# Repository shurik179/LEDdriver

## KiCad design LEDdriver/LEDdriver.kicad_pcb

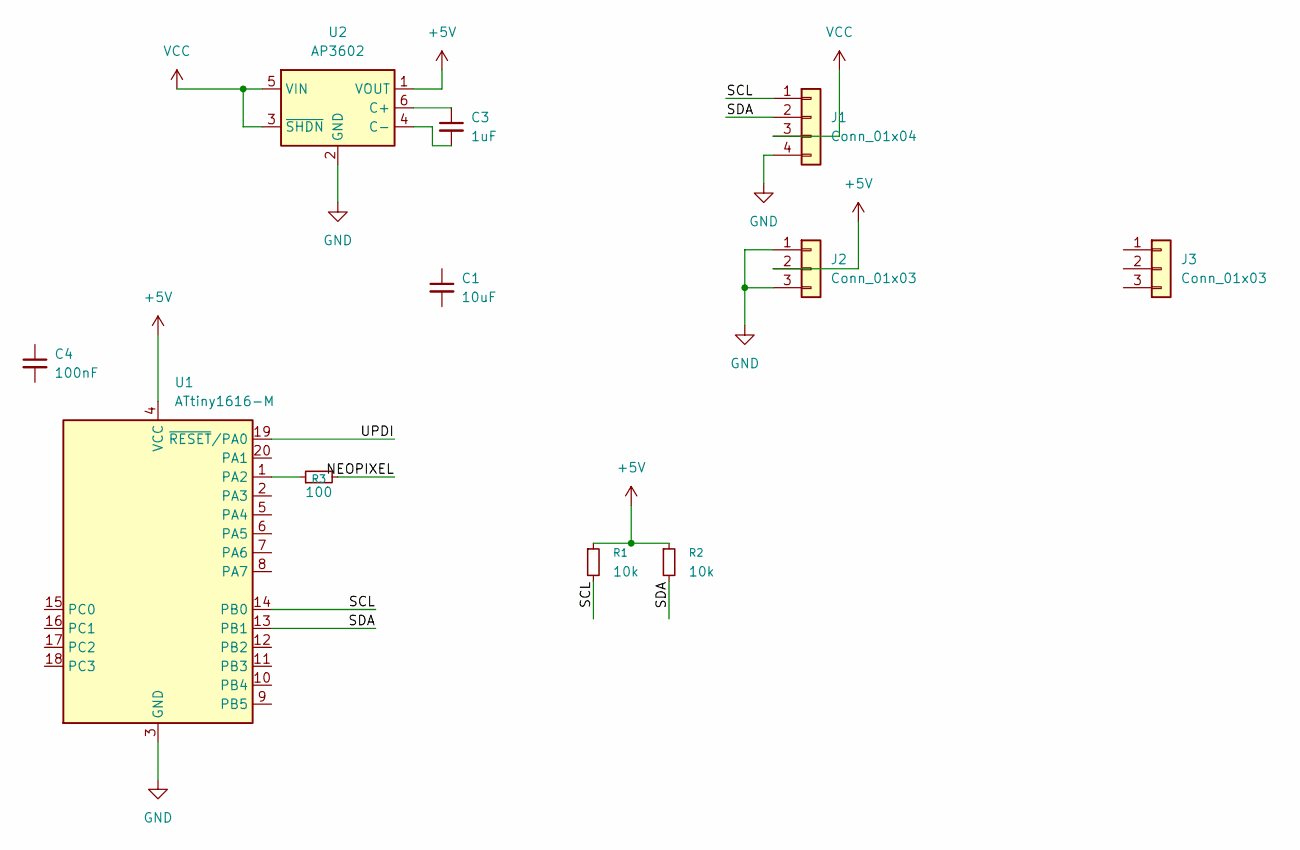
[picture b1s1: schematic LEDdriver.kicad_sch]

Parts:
C1: 10uF; C_0805_2012Metric
C3: 1uF; C_0603_1608Metric
C4: 100nF; C_0603_1608Metric
J1: Conn_01x04; JST_PH_S4B-PH-SM4-TB_1x04-1MP_P2.00mm_Horizontal
J2: Conn_01x03; PinHeader_1x03_P2.54mm_Horizontal
J3: Conn_01x03
R1, R2: 10k; R_0603_1608Metric
R3: 100; R_0603_1608Metric
U1: ATtiny1616-M; VQFN-20-1EP_3x3mm_P0.4mm_EP1.7x1.7mm
U2: AP3602; TSOT-23-6

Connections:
+5V: J2.2, R1.1, R2.1, U1.4 (VCC), U2.1 (VOUT)
/NEOPIXEL: R3.2
/SCL: J1.1, R1.2, U1.14 (PB0)
/SDA: J1.2, R2.2, U1.13 (PB1)
/UPDI: U1.19 (~RESET/PA0)
GND: J1.4, J2.1, J2.3, U1.3 (GND), U1.21 (GND), U2.2 (GND)
unnamed: R3.1, U1.1 (PA2)
unnamed: C3.1, U2.6 (C+)
unnamed: C3.2, U2.4 (C-)
VCC: J1.3, U2.3 (~SHDN), U2.5 (VIN)

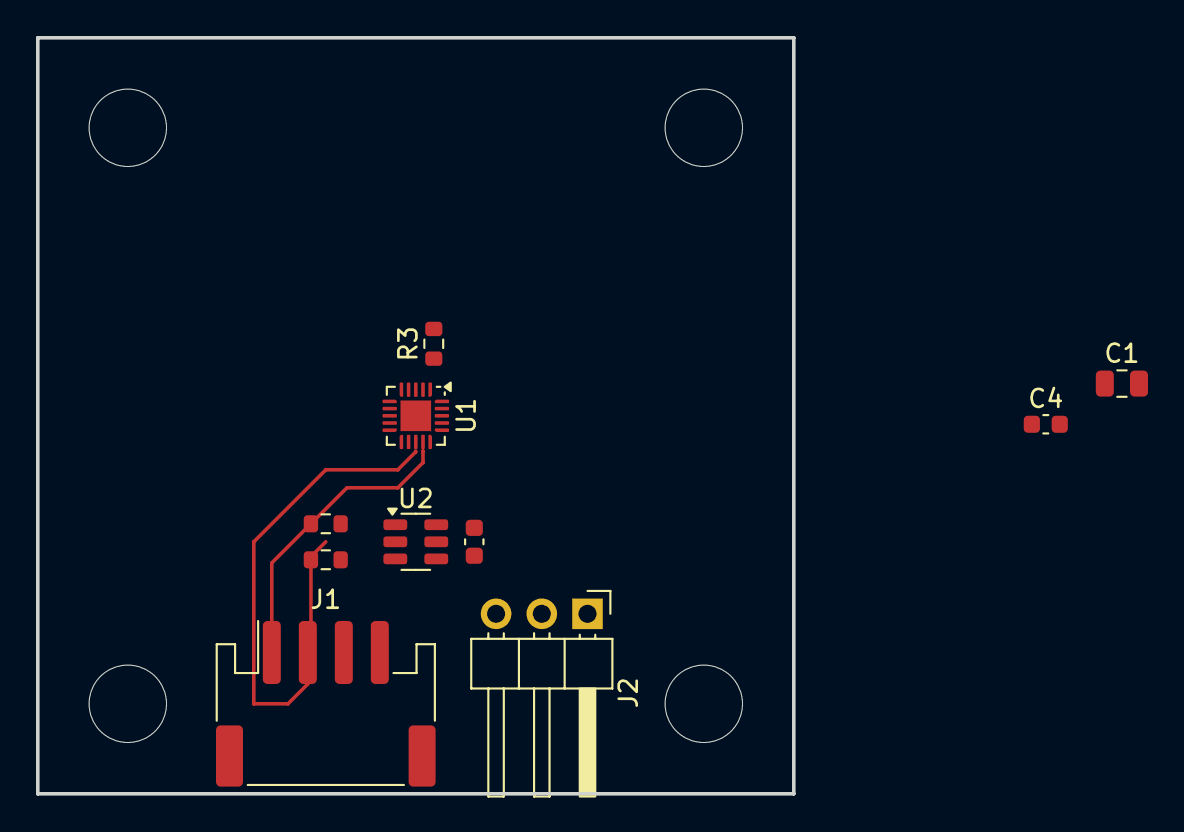
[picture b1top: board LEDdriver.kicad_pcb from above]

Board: 2 copper layers, 42.0 x 42.0 mm, 10 parts (0 on the bottom side), 8 nets.

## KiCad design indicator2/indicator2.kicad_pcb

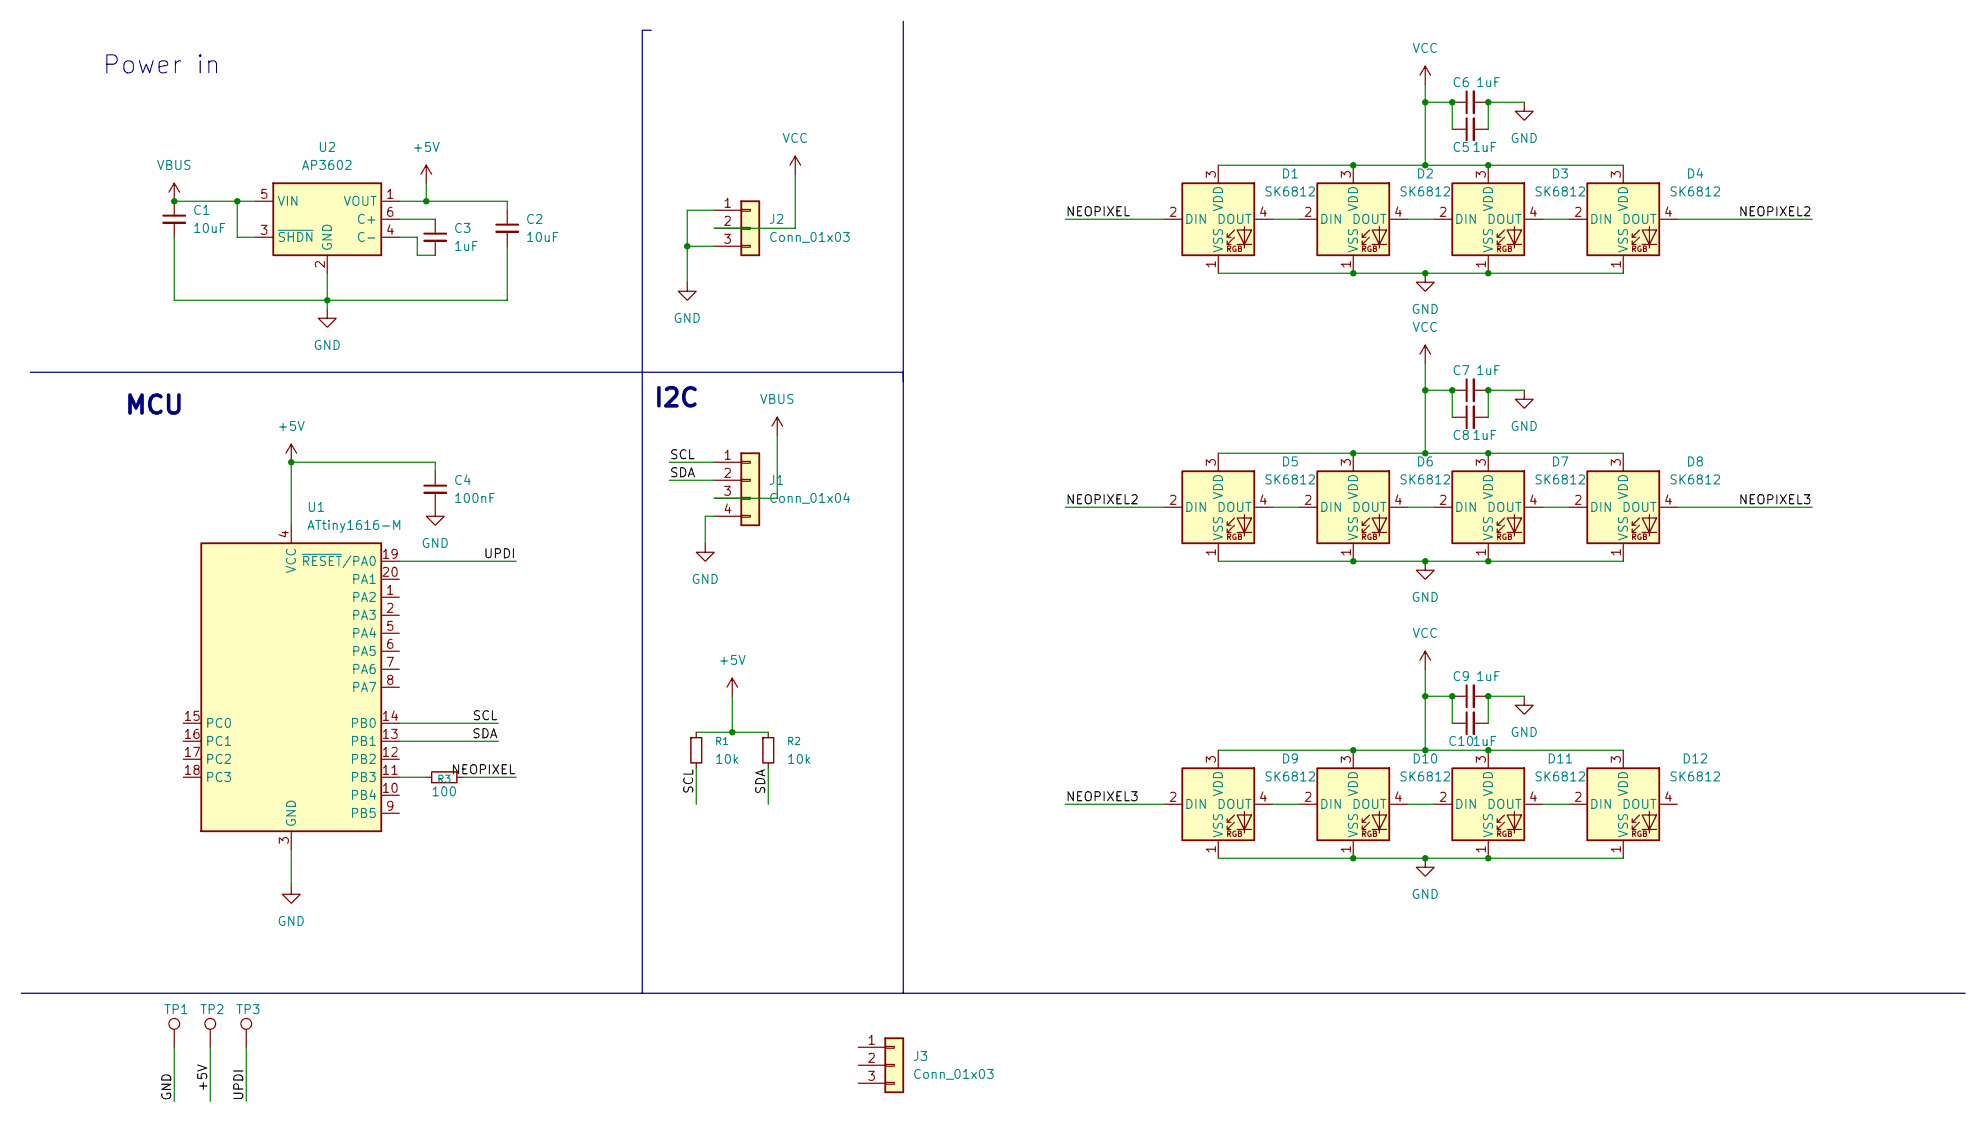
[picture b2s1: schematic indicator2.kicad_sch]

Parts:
C1, C2: 10uF; C_0805_2012Metric
C3, C5, C6, C7, C8, C9, C10: 1uF; C_0603_1608Metric
C4: 100nF; C_0603_1608Metric
D1, D2, D3, D4, D5, D6, D7, D8, D9, D10, D11, D12: SK6812; LED_SK6812_PLCC4_5.0x5.0mm_P3.2mm
J1: Conn_01x04; JST_PH_S4B-PH-SM4-TB_1x04-1MP_P2.00mm_Horizontal
J2: Conn_01x03; PinHeader_1x03_P2.54mm_Horizontal
J3: Conn_01x03
R1, R2: 10k; R_0603_1608Metric
R3: 100; R_0603_1608Metric
TP1, TP2, TP3: TestPoint; TestPoint_THTPad_D1.5mm_Drill0.7mm
U1: ATtiny1616-M; VQFN-20-1EP_3x3mm_P0.4mm_EP1.7x1.7mm
U2: AP3602; TSOT-23-6

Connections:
+5V: C2.1, C4.1, R1.1, R2.1, TP2.1, U1.4 (VCC), U2.1 (VOUT)
/NEOPIXEL: D1.2 (DIN), R3.2
/NEOPIXEL2: D4.4 (DOUT), D5.2 (DIN)
/NEOPIXEL3: D8.4 (DOUT), D9.2 (DIN)
/SCL: J1.1, R1.2, U1.14 (PB0)
/SDA: J1.2, R2.2, U1.13 (PB1)
/UPDI: TP3.1, U1.19 (~RESET/PA0)
GND: C1.2, C2.2, C4.2, C5.2, C6.2, C7.2, C8.2, C9.2, C10.2, D1.1 (VSS), D2.1 (VSS), D3.1 (VSS), D4.1 (VSS), D5.1 (VSS), D6.1 (VSS), D7.1 (VSS), D8.1 (VSS), D9.1 (VSS), D10.1 (VSS), D11.1 (VSS), D12.1 (VSS), J1.4, J2.1, J2.3, TP1.1, U1.3 (GND), U1.21 (GND), U2.2 (GND)
unnamed: D1.4 (DOUT), D2.2 (DIN)
unnamed: D2.4 (DOUT), D3.2 (DIN)
unnamed: D3.4 (DOUT), D4.2 (DIN)
unnamed: D5.4 (DOUT), D6.2 (DIN)
unnamed: D6.4 (DOUT), D7.2 (DIN)
unnamed: D7.4 (DOUT), D8.2 (DIN)
unnamed: D9.4 (DOUT), D10.2 (DIN)
unnamed: D10.4 (DOUT), D11.2 (DIN)
unnamed: D11.4 (DOUT), D12.2 (DIN)
unnamed: R3.1, U1.11 (PB3)
unnamed: C3.1, U2.6 (C+)
unnamed: C3.2, U2.4 (C-)
VBUS: C1.1, J1.3, U2.3 (~SHDN), U2.5 (VIN)
VCC: C5.1, C6.1, C7.1, C8.1, C9.1, C10.1, D1.3 (VDD), D2.3 (VDD), D3.3 (VDD), D4.3 (VDD), D5.3 (VDD), D6.3 (VDD), D7.3 (VDD), D8.3 (VDD), D9.3 (VDD), D10.3 (VDD), D11.3 (VDD), D12.3 (VDD), J2.2

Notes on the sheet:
I2C
MCU
Power in

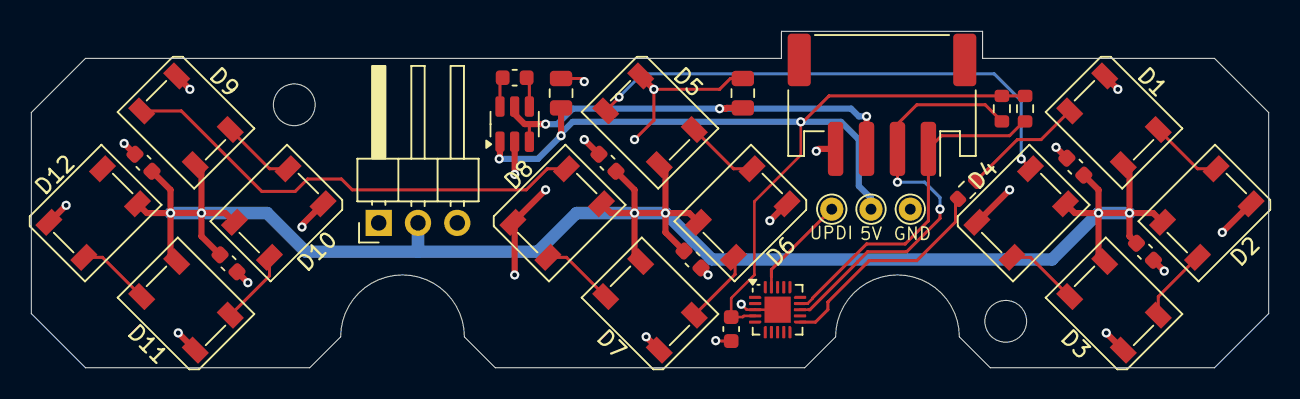
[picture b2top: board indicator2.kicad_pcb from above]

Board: 2 copper layers, 80.0 x 21.8 mm, 32 parts (0 on the bottom side), 22 nets.

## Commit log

2025-10-17 version2
